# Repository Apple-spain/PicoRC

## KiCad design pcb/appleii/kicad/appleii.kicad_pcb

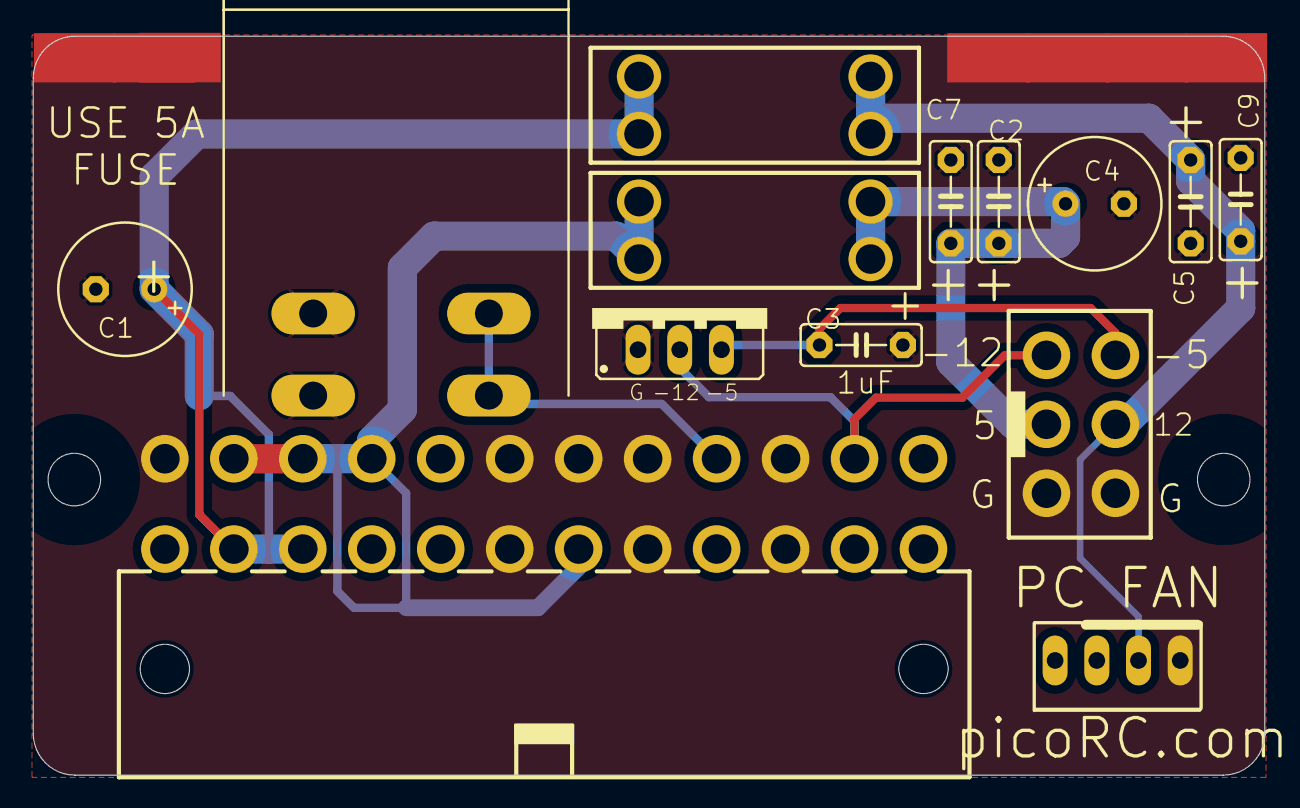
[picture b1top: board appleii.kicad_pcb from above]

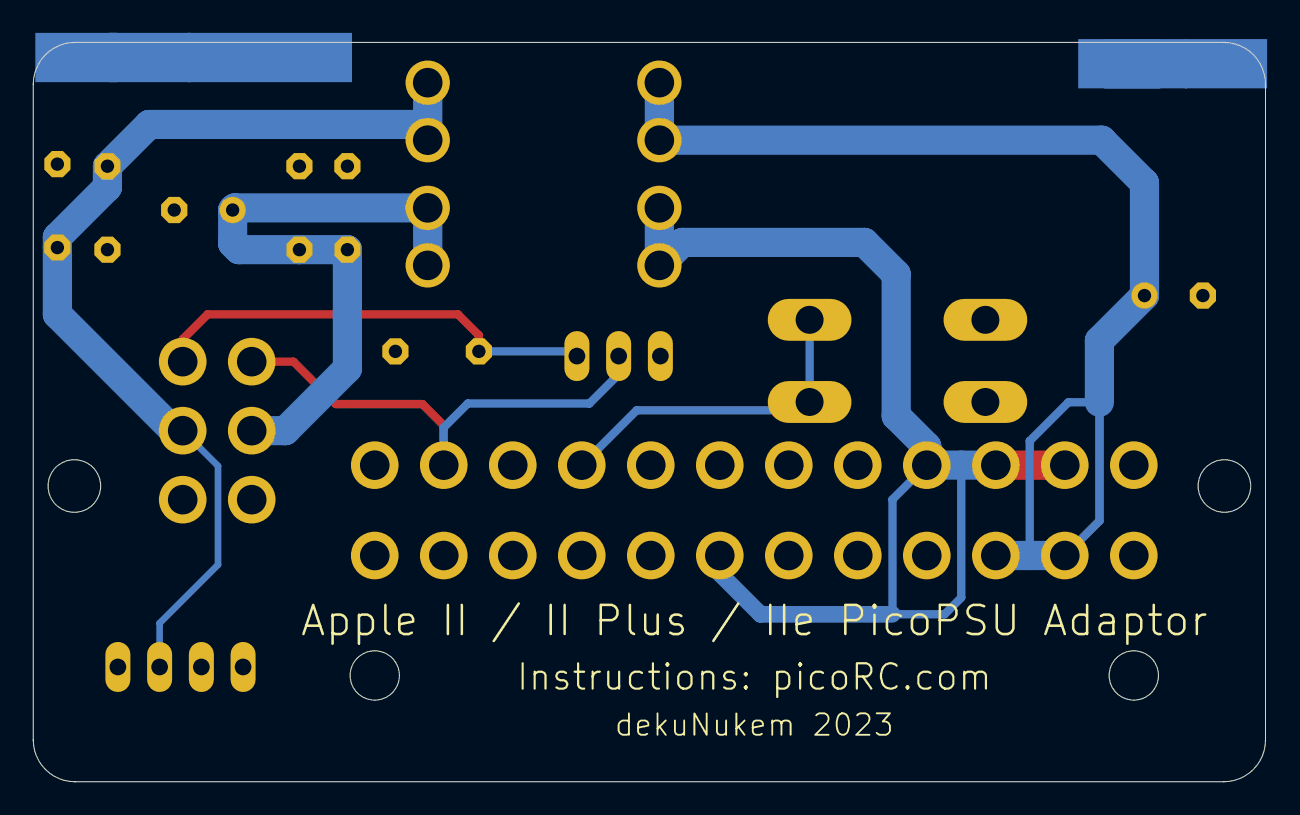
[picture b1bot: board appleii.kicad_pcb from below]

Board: 2 copper layers, 75.0 x 45.0 mm, 30 parts (7 on the bottom side), 8 nets.

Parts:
C1, C4: E3,5-8
C2, C3, C5, C7, C9: C5B2.5
IC1: 79XXS
J1: ATX24RH; ATX24_RIGHT_ANGLE
JP3: 1X04
U$1, U$2: CAR_FUSE_HOLDER3IN1; FUSE_HOLDER_3IN1
U$3: ROCK_SW; ROCK_SWITCH
U$4, U$5: M3_MOUNTING_HOLE; M3_MOUNTING_HOLE_PACK
U$6: APPLEII
U$7, U$8, U$9, U$10, U$11, U$12, U$13, U$14, U$15, U$16, U$17, U$18, U$19, U$20: EDGEPAD

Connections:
+5V: C2.1, C4.+, C7.1, U$1.A0, U$1.A1, U$6.3
+12V: C5.1, C9.1, JP3.2, U$2.B0, U$2.B1, U$6.4
-5V: C3.1, IC1.OUT, U$6.6
-12V: IC1.IN, J1.14, U$6.5
GND: C1.-, C2.2, C3.2, C4.-, C5.2, C7.2, C9.2, IC1.GND, J1.3, J1.5, J1.7, J1.15, J1.17, J1.18, J1.19, J1.24, JP3.1, U$3.P$1, U$3.P$3, U$6.1, U$6.2, U$7.P$1, U$8.P$1, U$9.P$1, U$10.P$1, U$11.P$1, U$12.P$1, U$13.P$1, U$14.P$1, U$15.P$1, U$16.P$1, U$17.P$1, U$18.P$1, U$19.P$1, U$20.P$1
unnamed: J1.16, U$3.P$2, U$3.P$4
unnamed: J1.6, J1.21, J1.22, J1.23, U$1.B0, U$1.B1
unnamed: C1.+, J1.10, J1.11, U$2.A0, U$2.A1

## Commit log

2023-11-20 añadiendo kicad y BOM
    añado los ficheros convertidos a KiCAD y el BOM en xlsx
